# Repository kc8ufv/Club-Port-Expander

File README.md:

# Club-Port-Expander

Atmega based port expander for RLC Club controllers

All inputs and outputs are level selectable. TX audio is passed only to the repeater port. RX audio is automatically switched with the main repeater port having priority. Audio is switched to only allow one source to pass at a time.

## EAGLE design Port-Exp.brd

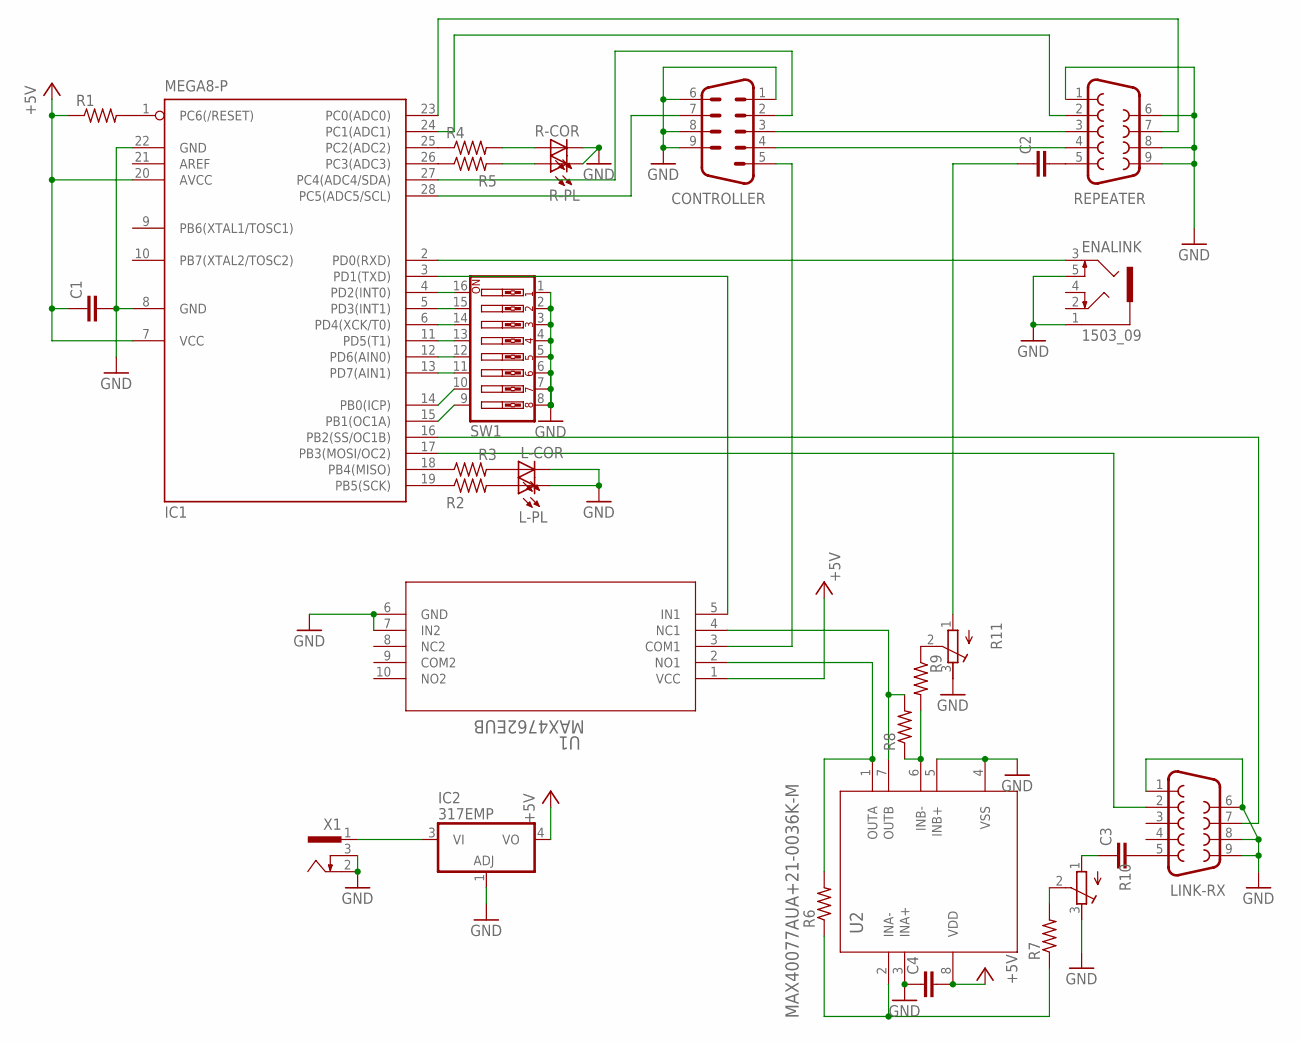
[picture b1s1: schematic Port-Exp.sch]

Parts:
C1, C2, C3, C4: C-EUC0402K; C0402K
CONTROLLER: M09D
ENALINK: 1503_09
IC1: MEGA8-P; DIL28-3
IC2: 317EMP; SOT223
L-COR: LEDCHIPLED_0805; CHIPLED_0805
L-PL: LEDCHIPLED_0805; CHIPLED_0805
LINK-RX: F09D
R1, R2, R3, R4, R5, R6, R7, R8, R9: R-US_M0805; M0805
R10, R11: R-TRIMM3339P; RTRIM3339P
R-COR: LEDCHIPLED_0805; CHIPLED_0805
R-PL: LEDCHIPLED_0805; CHIPLED_0805
REPEATER: F09D
SW1: SW_DIP-8; EDG-08
U1: MAX4762EUB; 21-0061L
U2: MAX40077AUA+21-0036K-M; 21-0036K-M
X1: SCD-014A; SCD-014-A

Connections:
+5V: C1.1, C4.2, IC1.7 (VCC), IC1.20 (AVCC), IC2.4 (VO), R1.1, U1.1 (VCC), U2.8 (VDD)
GND: C1.2, C4.1, CONTROLLER.1, CONTROLLER.6, CONTROLLER.8, CONTROLLER.9, ENALINK.1, ENALINK.5, IC1.8 (GND), IC1.22 (GND), IC2.1 (ADJ), L-COR.C, L-PL.C, LINK-RX.1, LINK-RX.6, LINK-RX.8, LINK-RX.9, R10.3 (E), R11.3 (E), R-COR.C, R-PL.C, REPEATER.1, REPEATER.6, REPEATER.8, REPEATER.9, SW1.1, SW1.2, SW1.3, SW1.4, SW1.5, SW1.6, SW1.7, SW1.8, U1.6 (GND), U1.7 (IN2), U2.3 (INA+), U2.4 (VSS), U2.5 (INB+), X1.2, X1.3
unnamed: CONTROLLER.2, IC1.27 (PC4(ADC4/SDA))
unnamed: CONTROLLER.7, IC1.28 (PC5(ADC5/SCL))
unnamed: IC1.17 (PB3(MOSI/OC2)), LINK-RX.2
unnamed: CONTROLLER.3, REPEATER.3
unnamed: CONTROLLER.4, REPEATER.4
unnamed: IC1.24 (PC1(ADC1)), REPEATER.2
unnamed: IC1.4 (PD2(INT0)), SW1.16
unnamed: IC1.3 (PD1(TXD)), U1.5 (IN1)
unnamed: IC1.16 (PB2(SS/OC1B)), LINK-RX.7
unnamed: CONTROLLER.5, U1.3 (COM1)
unnamed: IC1.23 (PC0(ADC0)), REPEATER.7
unnamed: IC1.5 (PD3(INT1)), SW1.15
unnamed: IC1.6 (PD4(XCK/T0)), SW1.14
unnamed: IC1.11 (PD5(T1)), SW1.13
unnamed: IC1.12 (PD6(AIN0)), SW1.12
unnamed: IC1.13 (PD7(AIN1)), SW1.11
unnamed: IC1.14 (PB0(ICP)), SW1.10
unnamed: IC1.15 (PB1(OC1A)), SW1.9
unnamed: IC1.1 (PC6(/RESET)), R1.2
unnamed: IC1.19 (PB5(SCK)), R2.1
unnamed: IC1.18 (PB4(MISO)), R3.1
unnamed: IC1.25 (PC2(ADC2)), R4.1
unnamed: IC1.26 (PC3(ADC3)), R5.1
unnamed: R4.2, R-COR.A
unnamed: R5.2, R-PL.A
unnamed: L-COR.A, R3.2
unnamed: L-PL.A, R2.2
unnamed: R6.2, U1.2 (NO1), U2.1 (OUTA)
unnamed: R8.2, U1.4 (NC1), U2.7 (OUTB)
unnamed: C2.2, REPEATER.5
unnamed: C3.2, LINK-RX.5
unnamed: R8.1, R9.2, U2.6 (INB-)
unnamed: R6.1, R7.1, U2.2 (INA-)
unnamed: R9.1, R11.2 (S)
unnamed: C3.1, R10.1 (A)
unnamed: R7.2, R10.2 (S)
unnamed: C2.1, R11.1 (A)
unnamed: ENALINK.3, IC1.2 (PD0(RXD))
unnamed: IC2.3 (VI), X1.1

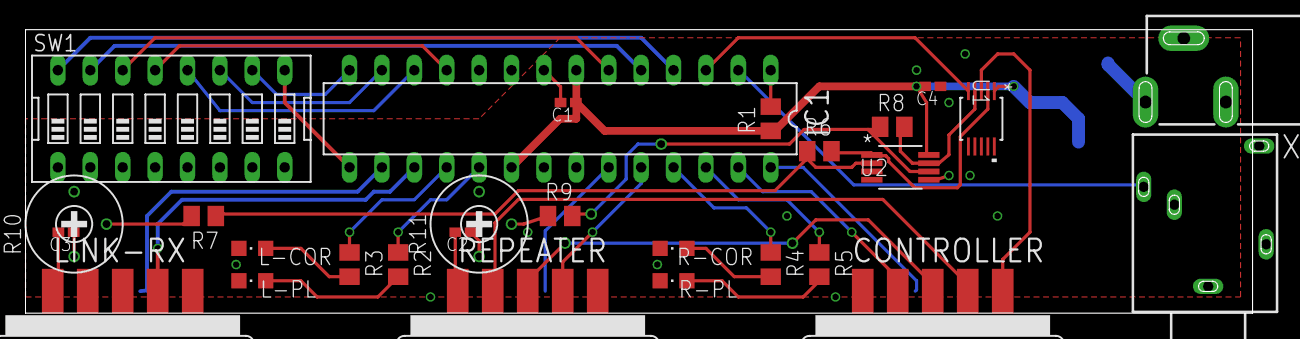
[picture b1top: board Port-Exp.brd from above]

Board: 2 copper layers, 97.7 x 22.2 mm, 29 parts (1 on the bottom side), 41 nets.

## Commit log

2019-10-15 removed .job files
2019-10-16 tweaked sizes, added label to board, adjusted schematic to print on one sheet
2019-11-01 Initial write of the code
2020-11-05 Update portexpander.ino
    Bugfixes - forgot to run digitalread on relevant pints to determine proper output polarity
